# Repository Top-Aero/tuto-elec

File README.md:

Tutoriel d'électronique
=======================

Projet d'électronique mêlant conception de circuit électronique et programmation de microcontrôleur.

Il est très largement inspiré de cette [vidéo youtube](https://www.youtube.com/watch?v=KPtmi16cyaA). Merci à Heliox.

# Plan

1. Dessiner le schéma électrique sur KiCAD
2. Concevoir le PCB sur KiCAD
3. Collaborer en partageant les fichiers sur GitHub
4. Si tout se passe bien, usiner les PCB au FabLab
5. Si tout se passe bien, trouver les composants au FabLab et les souder aux PCB

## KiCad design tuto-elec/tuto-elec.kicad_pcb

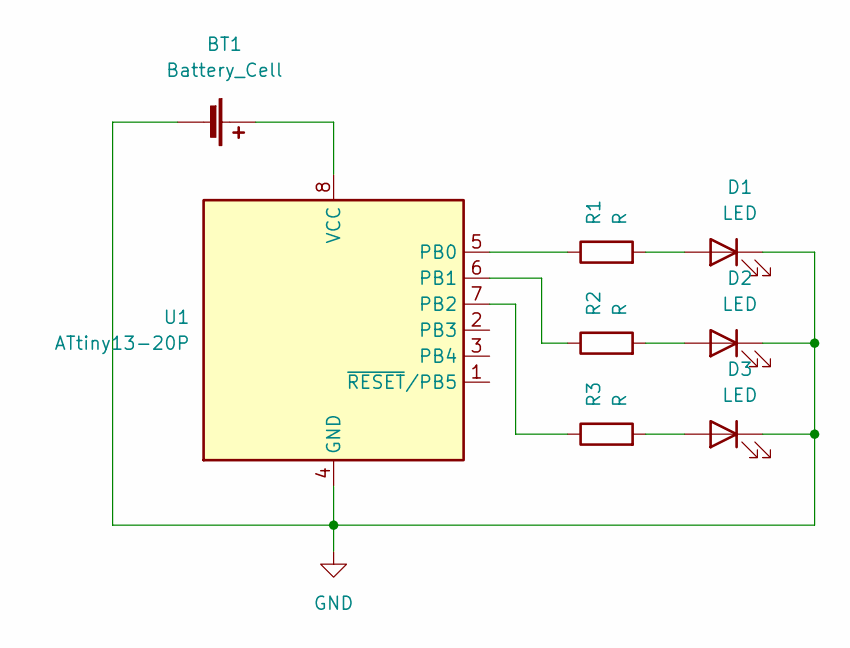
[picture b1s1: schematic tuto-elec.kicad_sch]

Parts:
BT1: Battery_Cell; BatteryHolder_Keystone_103_1x20mm
D1, D2, D3: LED; LED_D5.0mm
R1, R2, R3: R; R_2010_5025Metric
U1: ATtiny13-20P; DIP-8_W7.62mm

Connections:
GND: BT1.2 (-), D1.1 (K), D2.1 (K), D3.1 (K), U1.4 (GND)
unnamed: BT1.1 (+), U1.8 (VCC)
unnamed: D1.2 (A), R1.2
unnamed: D2.2 (A), R2.2
unnamed: D3.2 (A), R3.2
unnamed: R1.1, U1.5 (PB0)
unnamed: R2.1, U1.6 (PB1)
unnamed: R3.1, U1.7 (PB2)

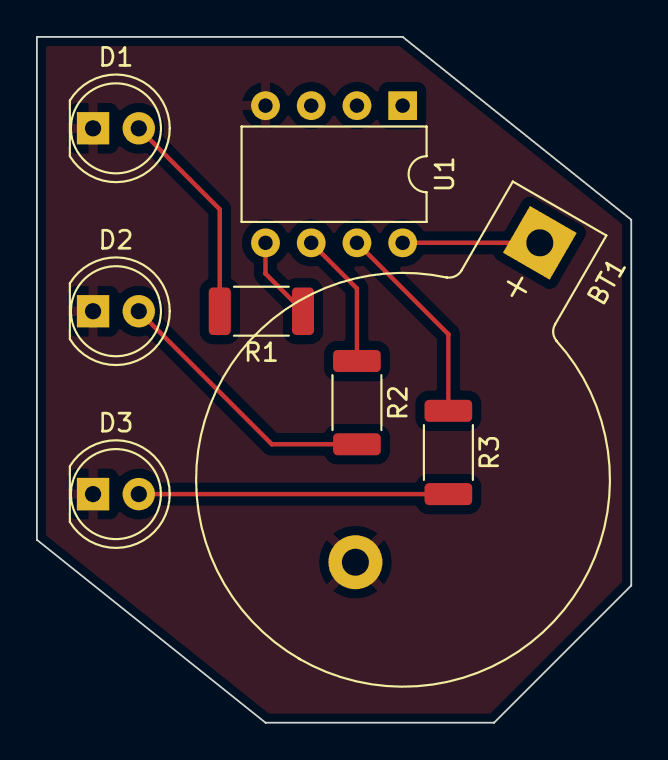
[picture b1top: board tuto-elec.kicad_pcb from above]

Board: 2 copper layers, 33.0 x 38.1 mm, 8 parts (0 on the bottom side), 8 nets.

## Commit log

2022-11-30 Rédiger un readme sommaire
2023-01-28 Create Haitam
2023-01-28 test ali
    test
2023-01-28 test
2023-01-28 ali branche
2023-01-28 mon commit
    ma description
